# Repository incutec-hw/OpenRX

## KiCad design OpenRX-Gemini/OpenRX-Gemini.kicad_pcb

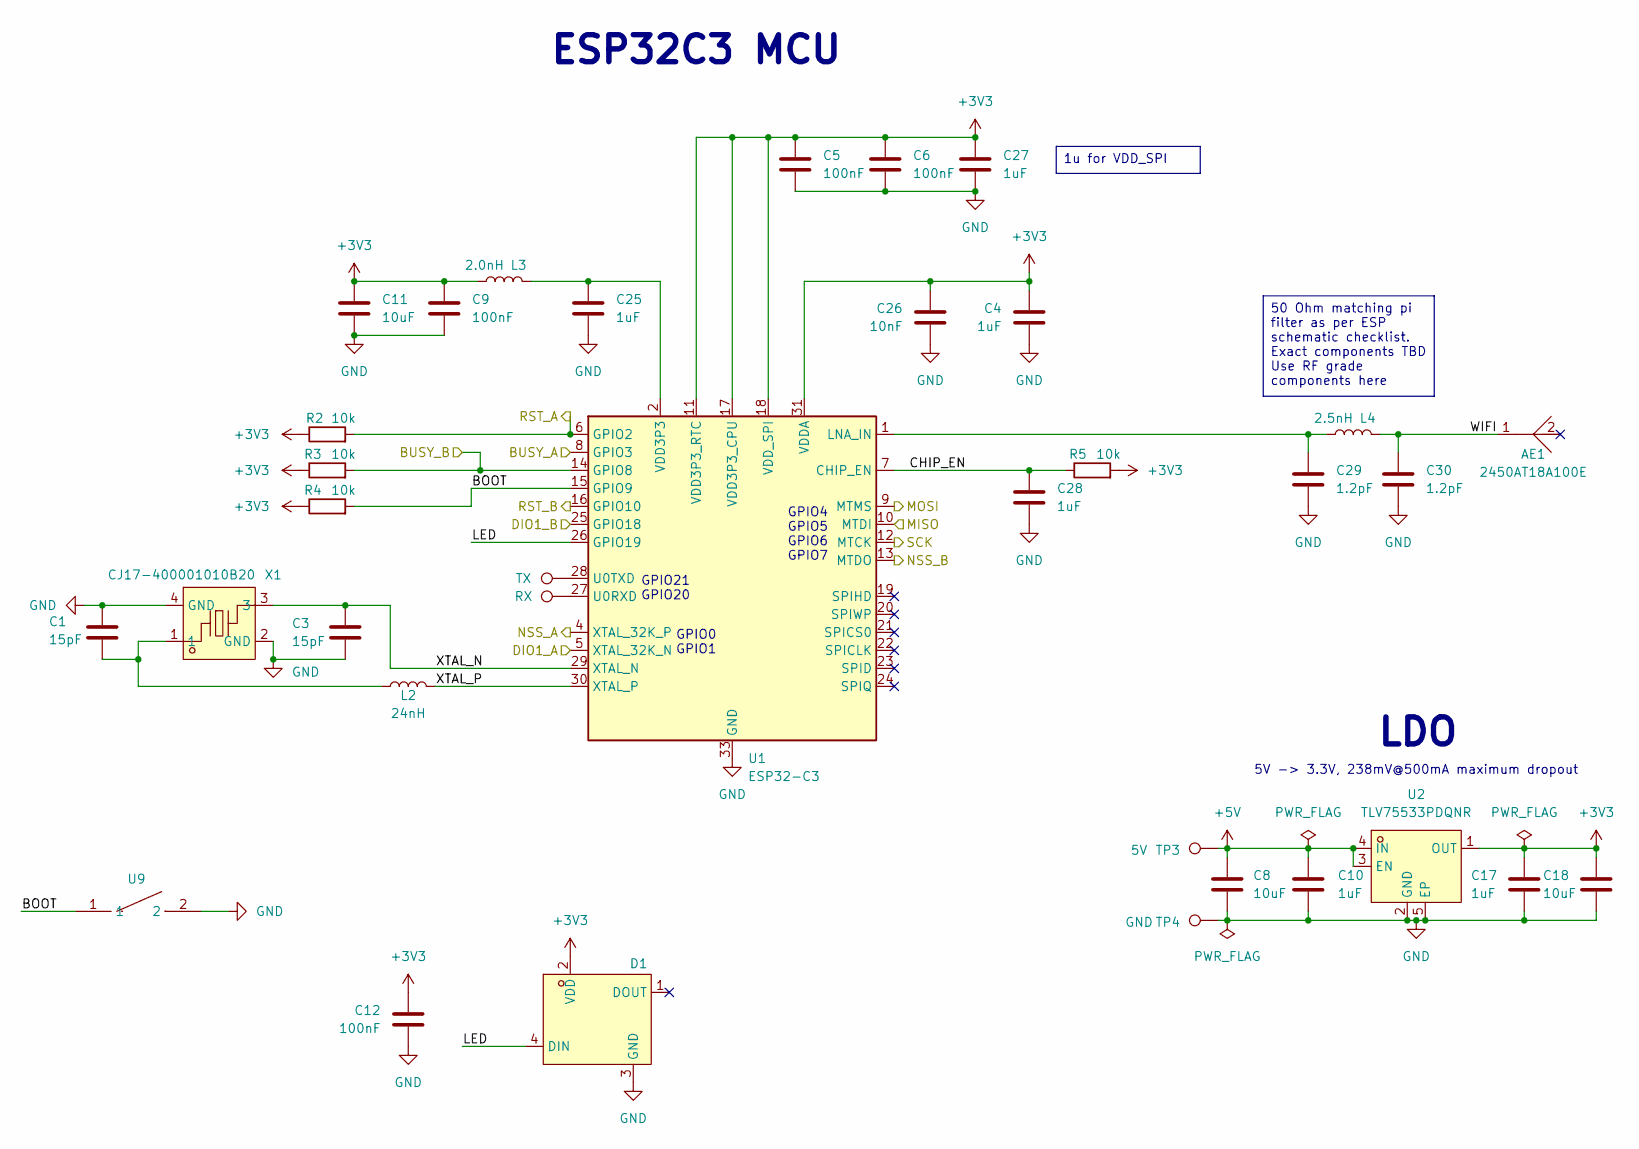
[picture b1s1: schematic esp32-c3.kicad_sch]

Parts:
AE1: 2450AT18A100E; ANT-SMD_L3.2-W1.6; LCSC Part C89334
C1, C3: 15pF; C_0201_0603Metric; LCSC C85891
C4, C10, C17, C25, C27, C28: 1uF; C_0201_0603Metric; LCSC C76935
C5, C6, C9, C12: 100nF; C_0201_0603Metric; LCSC C76939
C8, C18: 10uF; C_0402_1005Metric; LCSC C15525
C11: 10uF; C_0402_1005Metric; LCSC C76991
C26: 10nF; C_0201_0603Metric; LCSC C2168164
C29, C30: 1.2pF; C_0201_0603Metric; LCSC C85895
D1: XL-1010RGBC-WS2812B; LED-SMD_4P-L1.0-W1.0-TL_XL-1010RGBC-WS2812B; LCSC Part C5349953
L2: 24nH; L_0201_0603Metric; LCSC C206441
L3: 2.0nH; L_0201_0603Metric; LCSC C86125
L4: 2.5nH; L_0201_0603Metric; LCSC C206435
R2, R3, R4, R5: 10k; R_0201_0603Metric; LCSC C106225
TP1: RX; SolderPad_1.2x2.0mm
TP2: TX; SolderPad_1.2x2.0mm
TP3: 5V; SolderPad_1.2x2.0mm
TP4: GND; SolderPad_1.2x2.0mm
U1: ESP32-C3; QFN-32-1EP_5x5mm_P0.5mm_EP3.7x3.7mm
U2: TLV75533PDQNR; X2SON-4_L1.0-W1.0-P0.65-TL-EP; LCSC Part C2861882
U9: TS2306A 240GF MSM 9_C2976675; SW-SMD_4P-L3.0-W2.0-P0.85-LS3.5; LCSC Part C2976675
X1: CJ17-400001010B20; CRYSTAL-SMD_4P-L1.6-W1.2-BL; LCSC Part C2875272

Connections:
+3V3: C4.1, C5.1, C6.1, C9.1, C11.1, C12.1, C17.1, C18.1, C26.1, C27.1, D1.2 (VDD), L3.2, R2.1, R3.1, R4.1, R5.2, U1.11 (VDD3P3_RTC), U1.17 (VDD3P3_CPU), U1.18 (VDD_SPI), U1.31 (VDDA), U1.32 (VDDA), U2.1 (OUT); also elsewhere on the board
+5V: C8.1, C10.1, TP3.1 (1_1), U2.3 (EN), U2.4 (IN)
/ESP32-C3/BOOT: R4.2, U1.15 (GPIO9), U9.1
/ESP32-C3/BUSY_A: U1.8 (GPIO3); also elsewhere on the board
/ESP32-C3/BUSY_B: R3.2, U1.14 (GPIO8); also elsewhere on the board
/ESP32-C3/CHIP_EN: C28.1, R5.1, U1.7 (CHIP_EN)
/ESP32-C3/DIO1_A: U1.5 (XTAL_32K_N); also elsewhere on the board
/ESP32-C3/DIO1_B: U1.25 (GPIO18); also elsewhere on the board
/ESP32-C3/LED: D1.4 (DIN), U1.26 (GPIO19)
/ESP32-C3/MISO: U1.10 (MTDI); also elsewhere on the board
/ESP32-C3/MOSI: U1.9 (MTMS); also elsewhere on the board
/ESP32-C3/NSS_A: U1.4 (XTAL_32K_P); also elsewhere on the board
/ESP32-C3/NSS_B: U1.13 (MTDO); also elsewhere on the board
/ESP32-C3/RST_A: R2.2, U1.6 (GPIO2); also elsewhere on the board
/ESP32-C3/RST_B: U1.16 (GPIO10); also elsewhere on the board
/ESP32-C3/SCK: U1.12 (MTCK); also elsewhere on the board
/ESP32-C3/WIFI: AE1.1, C30.1, L4.1
/ESP32-C3/XTAL_N: C3.1, U1.29 (XTAL_N), X1.3
/ESP32-C3/XTAL_P: L2.2, U1.30 (XTAL_P)
GND: C1.2, C3.2, C4.2, C5.2, C6.2, C8.2, C9.2, C10.2, C11.2, C12.2, C17.2, C18.2, C25.2, C26.2, C27.2, C28.2, C29.2, C30.2, D1.3 (GND), TP4.1 (1_1), U1.33 (GND), U2.2 (GND), U2.5 (EP), U9.2, X1.2 (GND), X1.4 (GND); also elsewhere on the board
unnamed: C1.1, L2.1, X1.1
unnamed: C25.1, L3.1, U1.2 (VDD3P3), U1.3 (VDD3P3)
unnamed: C29.1, L4.2, U1.1 (LNA_IN)
unnamed: TP1.1 (1_1), U1.27 (U0RXD)
unnamed: TP2.1 (1_1), U1.28 (U0TXD)

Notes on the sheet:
ESP32C3 MCU
GPIO21 GPIO20
GPIO0 GPIO1
5V -> 3.3V, 238mV@500mA maximum dropout
GPIO4 GPIO5 GPIO6 GPIO7
LDO
50 Ohm matching pi filter as per ESP schematic checklist. Exact components TBD Use RF grade components here
1u for VDD_SPI

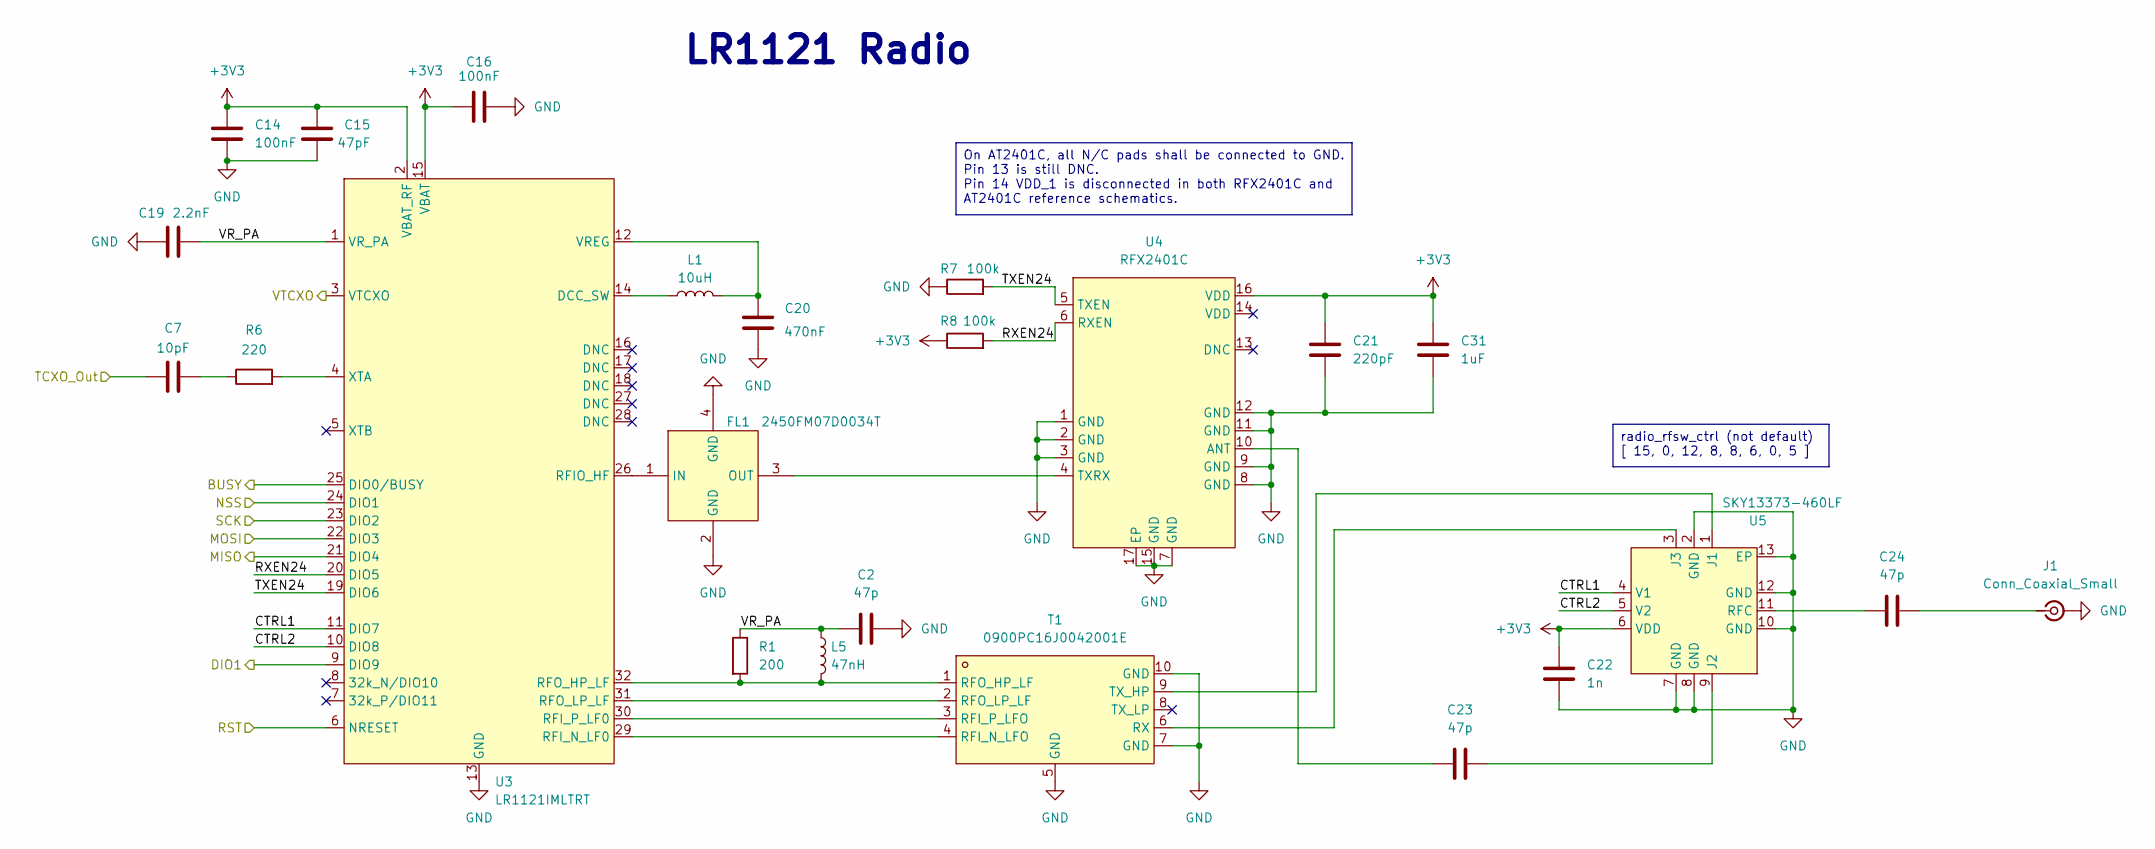
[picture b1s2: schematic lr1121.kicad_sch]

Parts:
C2, C23, C24: 47p; C_0201_0603Metric; LCSC C85908
C7: 10pF; C_0201_0603Metric; LCSC C384956
C14, C16: 100nF; C_0201_0603Metric; LCSC C76939
C15: 47pF; C_0201_0603Metric; LCSC C85908
C19: 2.2nF; C_0201_0603Metric; LCSC C161488
C20: 470nF; C_0201_0603Metric; LCSC C85926
C21: 220pF; C_0201_0603Metric; LCSC C907939
C22: 1n; C_0201_0603Metric; LCSC C85934
C31: 1uF; C_0201_0603Metric; LCSC C76935
FL1: 2450FM07D0034T; FILTER-SMD_4P-L1.0-W0.5-L; MPN 2450FM07D0034T; LCSC Part C2651081
J1: Conn_Coaxial_Small; U.FL_Hirose_U.FL-R-SMT-1_Vertical; LCSC C88374
L1: 10uH; L_0603_1608Metric; LCSC C194437
L5: 47nH; L_0402_1005Metric; LCSC C192855
R1: 200; R_0201_0603Metric; LCSC C274337
R6: 220; R_0201_0603Metric; LCSC C2074788
R7, R8: 100k; R_0201_0603Metric; LCSC C106224
T1: 0900PC16J0042001E; FILTER-SMD_10P-L2.0-W1.6-BL; LCSC Part C19842466
U3: LR1121IMLTRT; QFN-32-1EP_5x5mm_P0.5mm_EP3.7x3.7mm; LCSC Part C7498014
U4: RFX2401C; QFN-16_L3.0-W3.0-P0.50-BL-EP1.7; LCSC Part C19213
U5: SKY13373-460LF; QFN-12_EP_2x2_Pitch0.5mm

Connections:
+3V3: C14.1, C15.1, C16.1, C21.1, C22.1, C31.1, R8.1, U3.2 (VBAT_RF), U3.15 (VBAT), U4.16 (VDD), U5.6 (VDD); also elsewhere on the board
/Clock/TCXO_Out: C7.2; also elsewhere on the board
/ESP32-C3/BUSY_A: U3.25 (DIO0/BUSY); also elsewhere on the board
/ESP32-C3/DIO1_A: U3.9 (DIO9); also elsewhere on the board
/ESP32-C3/MISO: U3.21 (DIO4); also elsewhere on the board
/ESP32-C3/MOSI: U3.22 (DIO3); also elsewhere on the board
/ESP32-C3/NSS_A: U3.24 (DIO1); also elsewhere on the board
/ESP32-C3/RST_A: U3.6 (NRESET); also elsewhere on the board
/ESP32-C3/SCK: U3.23 (DIO2); also elsewhere on the board
/LR1121_A/CTRL1: U3.11 (DIO7), U5.4 (V1)
/LR1121_A/CTRL2: U3.10 (DIO8), U5.5 (V2)
/LR1121_A/RXEN24: R8.2, U3.20 (DIO5), U4.6 (RXEN)
/LR1121_A/TXEN24: R7.2, U3.19 (DIO6), U4.5 (TXEN)
/LR1121_A/VR_PA: C2.1, C19.1, L5.1, R1.1, U3.1 (VR_PA)
/LR1121_A/VTCXO: U3.3 (VTCXO)
GND: C2.2, C14.2, C15.2, C16.2, C19.2, C20.1, C21.2, C22.2, C31.2, FL1.2 (GND), FL1.4 (GND), J1.2 (Ext), R7.1, T1.5 (GND), T1.7 (GND), T1.10 (GND), U3.13 (GND), U3.33 (EP), U4.1 (GND), U4.2 (GND), U4.3 (GND), U4.7 (GND), U4.8 (GND), U4.9 (GND), U4.11 (GND), U4.12 (GND), U4.15 (GND), U4.17 (EP), U5.2 (GND), U5.7 (GND), U5.8 (GND), U5.10 (GND), U5.12 (GND), U5.13 (EP); also elsewhere on the board
unnamed: C7.1, R6.1
unnamed: FL1.1 (IN), U3.26 (RFIO_HF)
unnamed: FL1.3 (OUT), U4.4 (TXRX)
unnamed: C24.2, J1.1 (In)
unnamed: T1.4 (RFI_N_LFO), U3.29 (RFI_N_LF0)
unnamed: T1.3 (RFI_P_LFO), U3.30 (RFI_P_LF0)
unnamed: L5.2, R1.2, T1.1 (RFO_HP_LF), U3.32 (RFO_HP_LF)
unnamed: T1.2 (RFO_LP_LF), U3.31 (RFO_LP_LF)
unnamed: T1.6 (RX), U5.3 (J3)
unnamed: T1.9 (TX_HP), U5.1 (J1)
unnamed: L1.1, U3.14 (DCC_SW)
unnamed: C20.2, L1.2, U3.12 (VREG)
unnamed: R6.2, U3.4 (XTA)
unnamed: C23.1, U4.10 (ANT)
unnamed: C23.2, U5.9 (J2)
unnamed: C24.1, U5.11 (RFC)

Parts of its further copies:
C33: 2.2nF; C_0201_0603Metric; LCSC C161488
C34: 10pF; C_0201_0603Metric; LCSC C384956
C35, C37: 100nF; C_0201_0603Metric; LCSC C76939
C36: 47pF; C_0201_0603Metric; LCSC C85908
C38: 470nF; C_0201_0603Metric; LCSC C85926
C39, C42, C44: 47p; C_0201_0603Metric; LCSC C85908
C40: 220pF; C_0201_0603Metric; LCSC C907939
C41: 1uF; C_0201_0603Metric; LCSC C76935
C43: 1n; C_0201_0603Metric; LCSC C85934
FL2: 2450FM07D0034T; FILTER-SMD_4P-L1.0-W0.5-L; MPN 2450FM07D0034T; LCSC Part C2651081
J2: Conn_Coaxial_Small; U.FL_Hirose_U.FL-R-SMT-1_Vertical; LCSC C88374
L6: 10uH; L_0603_1608Metric; LCSC C194437
L7: 47nH; L_0402_1005Metric; LCSC C192855
R9: 220; R_0201_0603Metric; LCSC C2074788
R10: 200; R_0201_0603Metric; LCSC C274337
R11, R12: 100k; R_0201_0603Metric; LCSC C106224
T2: 0900PC16J0042001E; FILTER-SMD_10P-L2.0-W1.6-BL; LCSC Part C19842466
U6: LR1121IMLTRT; QFN-32-1EP_5x5mm_P0.5mm_EP3.7x3.7mm; LCSC Part C7498014
U7: RFX2401C; QFN-16_L3.0-W3.0-P0.50-BL-EP1.7; LCSC Part C19213
U8: SKY13373-460LF; QFN-12_EP_2x2_Pitch0.5mm

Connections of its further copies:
+3V3: C35.1, C36.1, C37.1, C40.1, C41.1, C43.1, R12.1, U6.2 (VBAT_RF), U6.15 (VBAT), U7.16 (VDD), U8.6 (VDD); also elsewhere on the board
/Clock/TCXO_Out: C34.2; also elsewhere on the board
/Clock/VTCXO: U6.3 (VTCXO); also elsewhere on the board
/ESP32-C3/BUSY_B: U6.25 (DIO0/BUSY); also elsewhere on the board
/ESP32-C3/DIO1_B: U6.9 (DIO9); also elsewhere on the board
/ESP32-C3/MISO: U6.21 (DIO4); also elsewhere on the board
/ESP32-C3/MOSI: U6.22 (DIO3); also elsewhere on the board
/ESP32-C3/NSS_B: U6.24 (DIO1); also elsewhere on the board
/ESP32-C3/RST_B: U6.6 (NRESET); also elsewhere on the board
/ESP32-C3/SCK: U6.23 (DIO2); also elsewhere on the board
/LR1121_B/CTRL1: U6.11 (DIO7), U8.4 (V1)
/LR1121_B/CTRL2: U6.10 (DIO8), U8.5 (V2)
/LR1121_B/RXEN24: R12.2, U6.20 (DIO5), U7.6 (RXEN)
/LR1121_B/TXEN24: R11.2, U6.19 (DIO6), U7.5 (TXEN)
/LR1121_B/VR_PA: C33.1, C39.1, L7.1, R10.1, U6.1 (VR_PA)
GND: C33.2, C35.2, C36.2, C37.2, C38.1, C39.2, C40.2, C41.2, C43.2, FL2.2 (GND), FL2.4 (GND), J2.2 (Ext), R11.1, T2.5 (GND), T2.7 (GND), T2.10 (GND), U6.13 (GND), U6.33 (EP), U7.1 (GND), U7.2 (GND), U7.3 (GND), U7.7 (GND), U7.8 (GND), U7.9 (GND), U7.11 (GND), U7.12 (GND), U7.15 (GND), U7.17 (EP), U8.2 (GND), U8.7 (GND), U8.8 (GND), U8.10 (GND), U8.12 (GND), U8.13 (EP); also elsewhere on the board
unnamed: C34.1, R9.1
unnamed: FL2.1 (IN), U6.26 (RFIO_HF)
unnamed: FL2.3 (OUT), U7.4 (TXRX)
unnamed: C44.2, J2.1 (In)
unnamed: T2.4 (RFI_N_LFO), U6.29 (RFI_N_LF0)
unnamed: T2.3 (RFI_P_LFO), U6.30 (RFI_P_LF0)
unnamed: L7.2, R10.2, T2.1 (RFO_HP_LF), U6.32 (RFO_HP_LF)
unnamed: T2.2 (RFO_LP_LF), U6.31 (RFO_LP_LF)
unnamed: T2.6 (RX), U8.3 (J3)
unnamed: T2.9 (TX_HP), U8.1 (J1)
unnamed: L6.1, U6.14 (DCC_SW)
unnamed: C38.2, L6.2, U6.12 (VREG)
unnamed: R9.2, U6.4 (XTA)
unnamed: C42.1, U7.10 (ANT)
unnamed: C42.2, U8.9 (J2)
unnamed: C44.1, U8.11 (RFC)

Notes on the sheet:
LR1121 Radio
radio_rfsw_ctrl (not default) [ 15, 0, 12, 8, 8, 6, 0, 5 ]
On AT2401C, all N/C pads shall be connected to GND. Pin 13 is still DNC. Pin 14 VDD_1 is disconnected in both RFX2401C and AT2401C reference schematics.

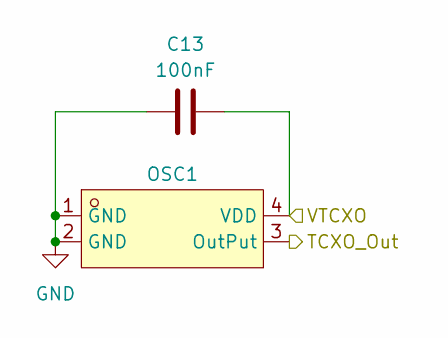
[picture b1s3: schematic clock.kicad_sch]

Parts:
C13: 100nF; C_0201_0603Metric; LCSC C76939
OSC1: OW7EL89CENUYO3YLC-32M; OSC-SMD_4P-L2.0-W1.6-BL_TXC_7Z; LCSC Part C22381772

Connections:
/Clock/TCXO_Out: OSC1.3 (OutPut); also elsewhere on the board
/Clock/VTCXO: C13.2, OSC1.4 (VDD); also elsewhere on the board
GND: C13.1, OSC1.1 (GND), OSC1.2 (GND); also elsewhere on the board

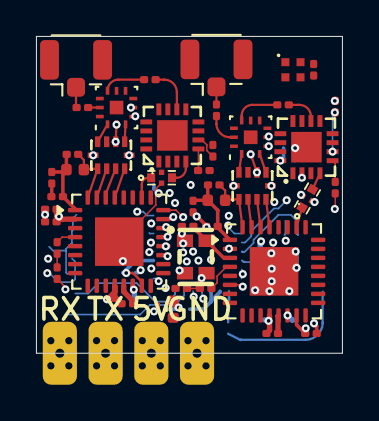
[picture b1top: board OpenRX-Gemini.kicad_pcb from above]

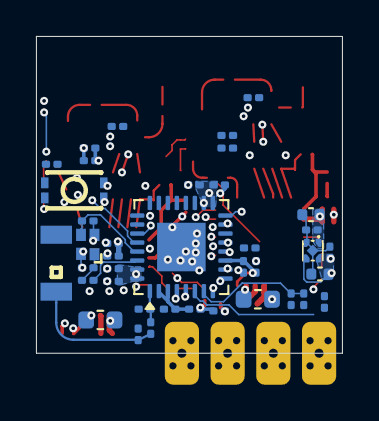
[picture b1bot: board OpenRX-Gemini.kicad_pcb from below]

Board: 6 copper layers, 17.0 x 17.6 mm, 85 parts (39 on the bottom side), 69 nets.

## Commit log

2026-05-08 gemini initial
2026-05-13 fab and placement output for combined order
